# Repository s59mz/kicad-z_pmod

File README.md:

# z_pmod
Adaptor from Z-Turn I/O Extension board to PMOD interfaces only

Schematic:
[z_pmod.pdf](z_pmod.pdf)

BOM:
[z_pmod.csv](z_pmod.csv)

Gerbers:
[gerbers.zip](https://github.com/s59mz/kicad-z_pmod/raw/main/gerbers.zip)

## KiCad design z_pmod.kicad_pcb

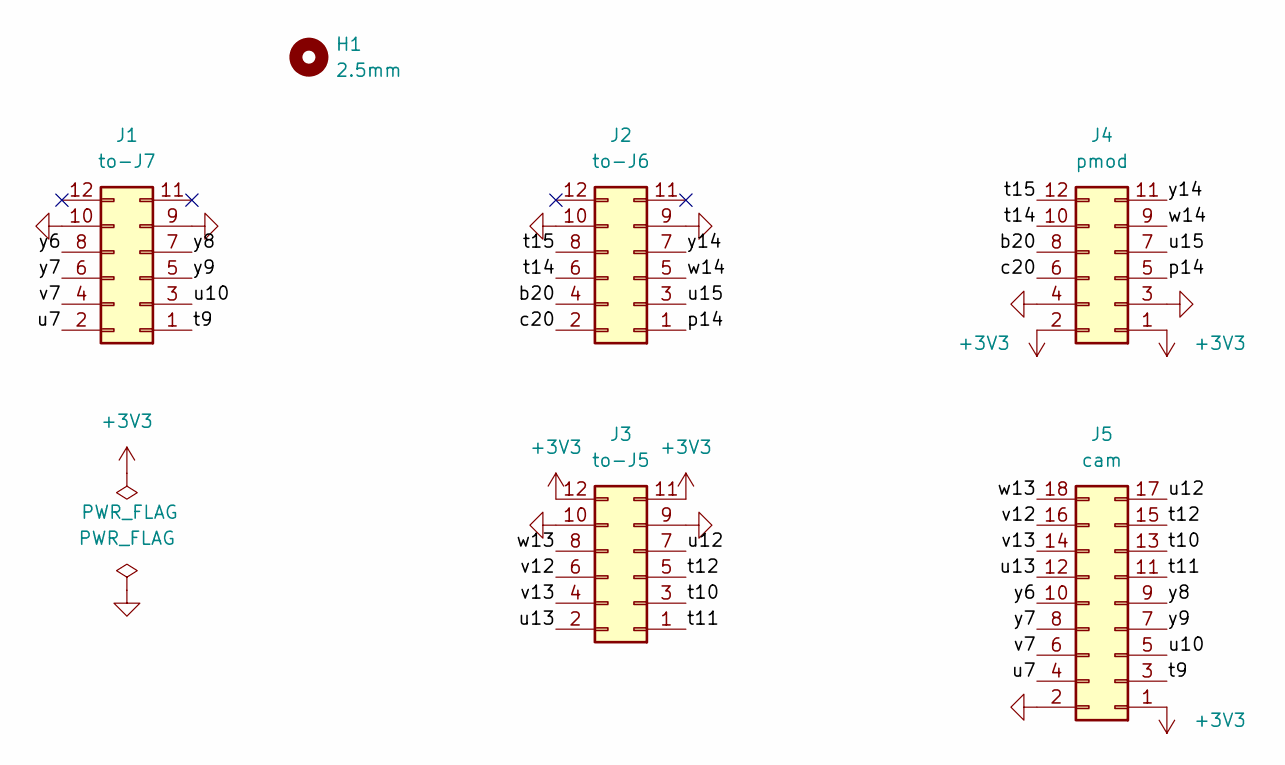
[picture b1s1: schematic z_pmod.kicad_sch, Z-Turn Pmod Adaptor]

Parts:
H1: 2.5mm; MountingHole_2.5mm
J1: to-J7; PinSocket_2x06_P2.54mm_Vertical
J2: to-J6; PinSocket_2x06_P2.54mm_Vertical
J3: to-J5; PinSocket_2x06_P2.54mm_Vertical
J4: pmod; PinSocket_2x06_P2.54mm_Horizontal
J5: cam; PinSocket_2x09_P2.54mm_Horizontal

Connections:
+3V3: J3.11, J3.12, J4.1, J4.2, J5.1
/b20: J2.4, J4.8
/c20: J2.2, J4.6
/p14: J2.1, J4.5
/t9: J1.1, J5.3
/t10: J3.3, J5.13
/t11: J3.1, J5.11
/t12: J3.5, J5.15
/t14: J2.6, J4.10
/t15: J2.8, J4.12
/u7: J1.2, J5.4
/u10: J1.3, J5.5
/u12: J3.7, J5.17
/u13: J3.2, J5.12
/u15: J2.3, J4.7
/v7: J1.4, J5.6
/v12: J3.6, J5.16
/v13: J3.4, J5.14
/w13: J3.8, J5.18
/w14: J2.5, J4.9
/y6: J1.8, J5.10
/y7: J1.6, J5.8
/y8: J1.7, J5.9
/y9: J1.5, J5.7
/y14: J2.7, J4.11
GND: J1.9, J1.10, J2.9, J2.10, J3.9, J3.10, J4.3, J4.4, J5.2

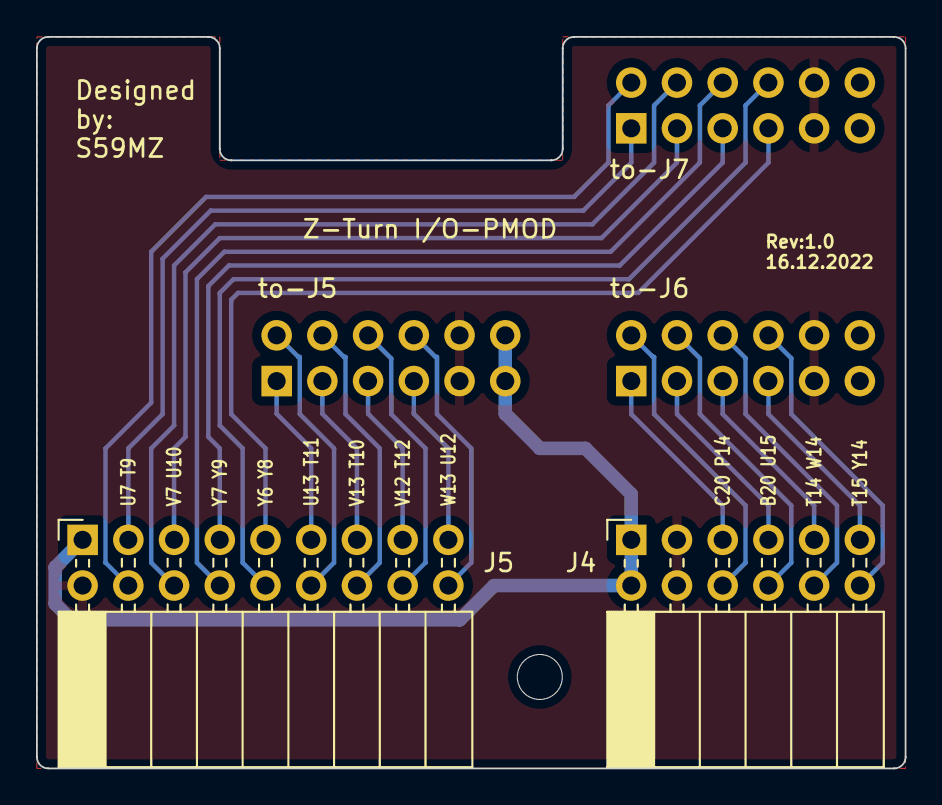
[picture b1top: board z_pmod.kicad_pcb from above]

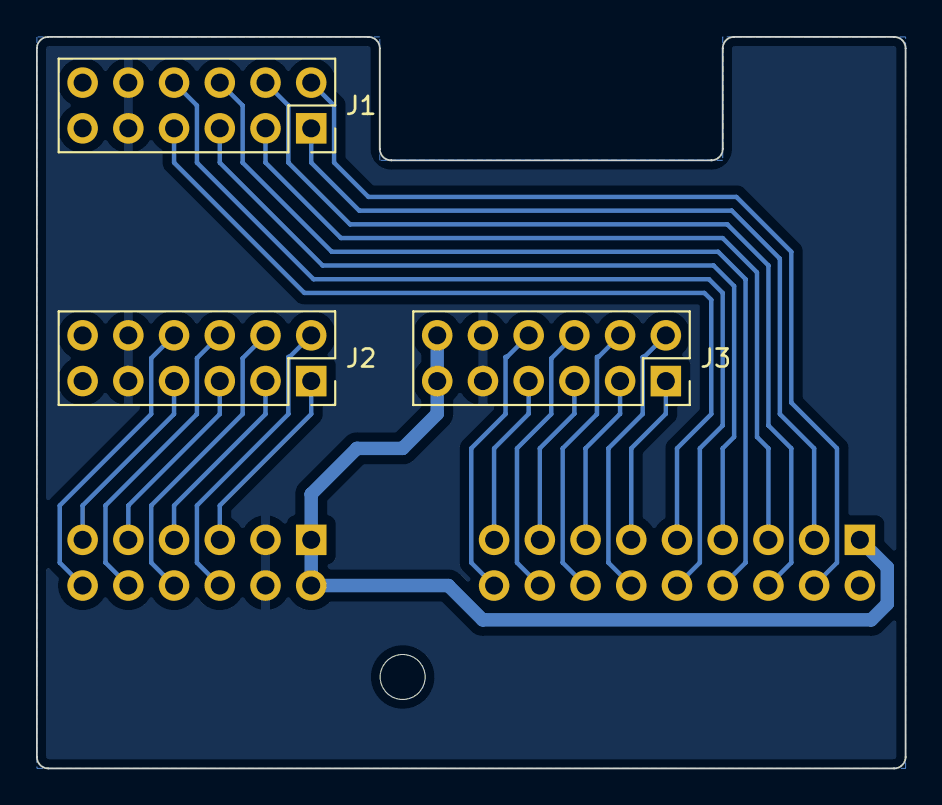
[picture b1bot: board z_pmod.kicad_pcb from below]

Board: 2 copper layers, 48.3 x 40.6 mm, 6 parts (3 on the bottom side), 26 nets.

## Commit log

2024-08-11 add screenshots
